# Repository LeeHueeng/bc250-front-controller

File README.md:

# BC250 Front Controller

**Turn your AMD BC-250 into a real PC** — smart power button, graceful shutdown, temperature-driven fan curve, OLED status display, and Home Assistant integration, all running standalone on a single ESP32-S3.

[🇰🇷 한국어 README](README.ko.md)

> ⚠️ **Status: work in progress.** Firmware boots and is verified on a bare board; full hardware validation (relay + sensors + fan on a live BC-250) is ongoing. Follow the repo for updates.

## Why?

The AMD BC-250 is a PS5-APU board that sells for roughly $100–150 these days — but it was born in a mining rack, so as a desktop it's missing everything:

- ❌ **No power button** and no ACPI — power on = PSU on
- ❌ **No graceful shutdown** — cutting power is the only "off"
- ❌ **No usable fan control** outside the original rack chassis
- ❌ **No status indication** whatsoever

This project fixes all of that with an ESP32-S3 sitting between your ATX PSU and the board — like the front panel the BC-250 never had.

## Features

- 🔌 **Real power button** — short press to power on / gracefully shut down, 5-second hold to force off
- 🛡️ **Fail-safe relay design** — the ATX `PS_ON` line is held through the relay's **NC contact**, so if the ESP32 crashes, reboots or updates, **your server stays up**
- 🧠 **Fully autonomous** — the graceful-shutdown sequence (HTTP request to the OS → wait → cut power), fan curve, OLED and button all run on the ESP32 itself. No Home Assistant, no cloud, no Wi-Fi required
- 🌡️ **Temperature-driven fan curve** — two DS18B20 probes (GPU heatsink + case), 25 kHz PWM, tach feedback with fan-failure detection
- 🖥️ **OLED status display** — power state, temperatures, fan RPM, network info on an SSD1306
- 🎛️ **On-device settings menu** — two extra buttons + the OLED give you a local menu: fan mode/preset, manual speed, display brightness, overheat threshold, shutdown timeout — all saved to flash, no phone or PC needed
- 🚨 **WS2812 status LED** — off / green (running) / yellow (shutting down) / red (fan failure, overheat)
- 🌐 **Built-in web dashboard** — control everything from a browser, straight from the ESP32
- 🏠 **Home Assistant auto-discovery** — appears natively via the ESPHome integration (optional MQTT)
- 📶 **Zero-config Wi-Fi provisioning** — first boot opens a `bc250-front-setup` AP with a captive portal; no credentials are baked into the firmware
- 🔄 **OTA updates** — flash over USB once, update over the air forever
- 📴 **Network-loss hardened** — never reboots on Wi-Fi/API loss; local control keeps working, the setup AP reopens automatically

## How it works

The BC-250 only uses the PCIe 8-pin — the ATX 24-pin connector is completely unused. So we steal three wires from it:

| ATX wire | Purpose |
|---|---|
| 🟣 Purple (pin 9, `5VSB`) | Always-on 5 V → powers the ESP32 + relay even when the PSU is "off" |
| 🟢 Green (pin 16, `PS_ON`) | Grounding this turns the PSU on — held via the relay **NC** contact |
| ⚪ Gray (pin 8, `PWR_OK`) | Tells the ESP32 whether the PSU is actually up (10k+10k divider) |

Graceful shutdown, with the **ESP32 as the source of truth** (no home-automation dependency):

```
button / web / HA  →  ESP32  →  HTTP shutdown request to the OS
                              →  wait 60 s for the OS to halt
                              →  release PS_ON (power off)
```

## Build tiers — everything is optional except the relay

Missing parts don't break anything: an absent OLED, sensor, fan or button simply disables that one feature. Start minimal, add parts whenever you feel like it.

| Tier | Hardware | You get | Firmware |
|---|---|---|---|
| **Minimal** | ESP32 + relay + 3 jumper wires | Web/HA power on-off, graceful shutdown, status LED (onboard) | [`bc250-front-minimal.yaml`](bc250-front-minimal.yaml) |
| **+ Button** | + push button | Physical front-panel power button | same |
| **Full** | + OLED, 2× DS18B20, PWM fan, 2 menu buttons, PWR_OK divider | Fan curve, temperatures, display, on-device settings menu, PSU state | [`bc250-front.yaml`](bc250-front.yaml) |
| **Full + color LCD** | Full, but OLED → **ST7789V 2.4" 240×320 SPI** | All of the above + large color UI, status icons, backlight dimming | [`bc250-front-st7789.yaml`](bc250-front-st7789.yaml) |

## Hardware

| Part | Qty | ~Cost |
|---|---|---|
| ESP32-S3 dev board (2×22 pins) | 1 | $5 |
| 5 V 1-channel relay module (optocoupler) | 1 | $1 |
| SSD1306 0.96" OLED (I2C) | 1 | $2 |
| DS18B20 temperature sensor | 2 | $2 |
| Momentary push button (power + 2 menu) | 3 | $1 |
| Resistors: 2× 10 kΩ, 1× 4.7 kΩ | — | $0.1 |
| Dupont jumper wires | — | $1 |

**No soldering required** — male jumper pins fit straight into the unused ATX 24-pin connector holes.

## PCB — three options (optional)

| | [**DIY carrier board**](hardware/bc250-front-carrier/README.md) | [**Semi-assembled PCBA**](hardware/bc250-front-pcba/README.md) | [**DevKit mini**](hardware/bc250-front-mini/README.md) |
|---|---|---|---|
| How | bare board, hand-solder the parts, plug in an ESP32-S3-DevKitC-1 | JLCPCB Economic assembly — you solder only the ESP32-S3 WROOM module, the display socket and (optionally) the LED | **66×50 mm**, smallest — DevKit on sockets, parts under it, LCD wired to a pin header |
| Power switch | relay | MOSFET (silent) | MOSFET (silent) |
| Sensors | DS18B20 | DS18B20 **or** 10 kΩ NTC | DS18B20 |
| Cost (5 boards) | ≈ $2 boards + ≈ $8 parts each | JLCPCB ≈ $45 + ≈ $4 module each → ≈ $13 each | ≈ $2 boards (≈ $12 with SMD assembly) + a DevKit |
| Firmware | `relay_inverted: "false"` | defaults + `log_uart: USB_SERIAL_JTAG` | defaults (`relay_inverted: "true"`) |

All three take the PSU's ATX 24-pin plug directly and use the pin map above.

## Wiring

| ESP32-S3 pin | Connects to |
|---|---|
| `5V` | ATX pin 9 — purple `5VSB` |
| `GND` | ATX black (common ground) |
| `3V3` | OLED VCC, DS18B20 VDD, pull-ups |
| `GPIO4` | Relay IN |
| `GPIO5` | ATX pin 8 — gray `PWR_OK` (**via 10k+10k divider**) |
| `GPIO6` | Power button (other leg → GND) |
| `GPIO7` | DS18B20 data ×2, 4.7 kΩ pull-up to 3.3 V |
| `GPIO8` / `GPIO9` | OLED SDA / SCL |
| `GPIO10` | Fan PWM (4-pin fan, pin 4) |
| `GPIO11` | Fan tach (4-pin fan, pin 3) |
| `GPIO12` / `GPIO13` | Menu buttons A (navigate) / B (select) — other leg → GND |
| `GPIO48` | WS2812 (onboard on most devkits) |

Relay contacts: **COM ↔ ATX pin 16 (green `PS_ON`)**, **NC ↔ GND**, NO unused.

Full interactive wiring guide (Korean): [`docs/wiring-guide.html`](docs/wiring-guide.html) (OLED) · [`docs/wiring-guide-st7789.html`](docs/wiring-guide-st7789.html) (ST7789V)

## Flashing

```bash
pip install esphome
esphome run bc250-front.yaml   # first time over USB, afterwards OTA
```

First boot: join the **`bc250-front-setup`** Wi-Fi AP from your phone → the captive portal opens → pick your network, enter the password. Done. Home Assistant will auto-discover the device within minutes.

> **Board note:** on CH343-based devkits the logger must use `hardware_uart: UART0` (already set in the YAML) — the default USB-JTAG console is not routed to the USB port on those boards.

## Roadmap

- [ ] OS-side shutdown agent (tiny systemd unit) + install script
- [ ] INA226 power monitoring (watts on the OLED!)
- [ ] Web-editable fan curve
- [ ] 3D-printable front-panel enclosure
- [ ] Buzzer alerts / event log

PRs and issues welcome — especially test reports from different BC-250 setups.

## Credits

- [mothenjoyer69/bc250-documentation](https://github.com/mothenjoyer69/bc250-documentation) — the definitive BC-250 hardware reference
- [elektricM/amd-bc250-docs](https://github.com/elektricM/amd-bc250-docs) — power & cooling documentation
- Built with [ESPHome](https://esphome.io)

## License

[MIT](LICENSE)

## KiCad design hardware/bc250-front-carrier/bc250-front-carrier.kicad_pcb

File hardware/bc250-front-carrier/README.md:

# BC250 Front Controller — carrier PCB v1.0

A carrier board for the ESP32-S3-DevKitC-1. **The PSU's ATX 24-pin plug goes straight onto the board**, so 5VSB / PS_ON / PWR_OK / 12V / GND are wired without jumper wires or hot glue. Every part is through-hole — a soldering iron is all you need.

[🇰🇷 한국어](README.ko.md)

| | |
|---|---|
| Size | 96 × 64 mm, 2 layers, 1.6 mm, 4× M3 holes (87 × 55 mm spacing) |
| MCU | ESP32-S3-DevKitC-1 (2×22 pins) in two female sockets |
| Power | ATX 24-pin header (Molex Mini-Fit Jr 5566-24A) on board |
| Relay | SRD-05VDC-SL-C + S8050 NPN driver on board — same **NC fail-safe** wiring as before |
| Display | ST7789 2.4″ SPI 8-pin socket **and** SSD1306 OLED 4-pin socket (fit either) |
| Other connectors | 4-pin PWM fan, 2× DS18B20, external WS2812, 6-pin front-panel buttons + 3 on-board tact switches |
| Checks | KiCad 10 ERC / DRC / schematic-PCB parity: **0 violations** (not yet verified on a physical board — see first power-up below) |

## Files

| File | Purpose |
|---|---|
| [`gerbers/bc250-front-carrier-v1.0-gerbers.zip`](gerbers/bc250-front-carrier-v1.0-gerbers.zip) | **upload this to JLCPCB** (Gerbers + Excellon drill + job file) |
| `bc250-front-carrier.kicad_pro` / `.kicad_sch` / `.kicad_pcb` | KiCad 10 project, footprint and symbol libraries included (opens anywhere) |
| [`bc250-front-carrier-schematic.pdf`](bc250-front-carrier-schematic.pdf) | schematic |
| [`bom.csv`](bom.csv) | bill of materials |
| `bc250-front-carrier-pos.csv` | component positions (assembly reference) |
| `images/` | top / bottom / iso renders, layout SVG, schematic SVG |
| [`../tools/`](../tools/) | regenerates the whole board from scripts (`build.sh`) |

## Ordering at JLCPCB

1. [jlcpcb.com](https://jlcpcb.com) → **Order now** → *Add gerber file* → upload `gerbers/bc250-front-carrier-v1.0-gerbers.zip`
2. It is detected as 96 × 64 mm, 2 layers. Keep the **defaults**: FR-4, 1.6 mm, 1 oz, HASL, quantity 5 (colour is up to you, Remove Order Number: No).
3. No SMT assembly needed — everything is hand-soldered.
4. Expect roughly $2 for 5 boards plus shipping.

## BOM

| Ref | Qty | Part | Notes |
|---|---|---|---|
| U1 | 1 | ESP32-S3-DevKitC-1 (N8R2 / N16R8, either) | with male pin headers soldered |
| U1 sockets | 2 | 1×22 female pin socket 2.54 mm | solder with the DevKit plugged in for alignment |
| J1 | 1 | ATX 24-pin motherboard header (Molex 5566-24A / 39-28-1243 or compatible, 4.2 mm 2×12 vertical) | |
| K1 | 1 | SRD-05VDC-SL-C relay (Songle / Sanyou SRD) | |
| Q1 | 1 | S8050 NPN (2N2222A / BC337 also fine) | TO-92, E-B-C |
| D1 | 1 | 1N4148 | cathode band toward the **K** mark |
| R1 | 1 | 1 kΩ | |
| R2, R3, R4 | 3 | 10 kΩ | |
| R5 | 1 | 4.7 kΩ | |
| C1 | 1 | 100 µF 16 V electrolytic (5 mm) | long leg (+) to the **+** mark |
| C2 | 1 | 100 nF ceramic | |
| J2 | 1 | 1×8 female pin socket | ST7789 LCD module plugs in directly |
| J3 | 1 | 1×4 female pin socket | SSD1306 OLED module plugs in directly |
| J4 | 1 | 1×4 male pin header | 4-pin fan (a real fan header fits too) |
| J5, J6, J7 | 3 | 1×3 male pin header | 2× DS18B20, WS2812 |
| J8 | 1 | 1×6 male pin header | front-panel buttons (optional) |
| SW1–SW3 | 3 | 6×6 mm tactile switch | on-board PWR / A / B |
| H1–H4 | 4 | M3 standoffs | optional |

## Assembly order

1. **Low parts first**: R1–R5 → D1 (band to `K`) → Q1 (flat side as drawn on the silkscreen) → C2 → C1 (mind the `+`)
2. **Sockets and headers**: J2/J3 female sockets, J4–J8 pin headers, SW1–SW3, the two 1×22 sockets for U1
3. **Big parts**: K1 relay, J1 ATX header — the latch ramp faces the top board edge (the `ATX 24-pin ← PSU plug` text)

## ⚠️ First power-up — **before** fitting the ESP32

The ATX header pin numbering follows KiCad's standard Molex 5566-24A footprint, but no physical board has been verified yet. This takes a minute:

1. Plug in the PSU's 24-pin **without** the DevKit and switch the PSU on. The relay is idle (NC), so **the PSU turning on immediately is correct** — that is the fail-safe.
2. With a multimeter (also printed on the back silkscreen):
   - U1 socket, top row `5V` pin ↔ `GND` = **about 5 V**
   - `FAN` header `12V` pin ↔ `GND` = **12 V**
   - If the `5V` pin reads 0 V or 12 V, **stop** and check J1 orientation/solder joints.
3. Power the PSU off and fit the DevKit: USB connectors toward the **left board edge** (`USB` silkscreen), antenna toward the relay.

## Firmware

- Set **`relay_inverted: "false"`** under `substitutions:` in the yaml (this board drives the relay with an NPN, active-high; off-the-shelf relay modules are `"true"`).
- If you attach an external WS2812 to J7, adjust `num_leds` in `light:` (the DevKit's on-board LED is pixel 0).
- Everything else matches the [wiring guide](../../docs/wiring-guide.html) — the board simply implements that wiring.

## Design notes

- **Relay**: COM=PS_ON, NC=GND. PS_ON is grounded at rest, so the PSU is on. GPIO4 HIGH → Q1 → coil energised → NC opens → PSU off. R2 (10 k) keeps the coil off while the ESP32 boots; D1 clamps the flyback. NO is left open.
- **PWR_OK**: 5 V → R3/R4 10 k/10 k → 2.5 V → GPIO5.
- **1-Wire**: GPIO7 with R5 4.7 k to 3V3; both DS18B20s in parallel on J5/J6.
- **Power**: 5VSB → DevKit `5V` pin (on-board LDO) + relay coil (C1 100 µF). 3V3 from the DevKit LDO feeds J2/J3/J5/J6/R5. 12 V is fan-only (present only while the PSU is on).
- **Layout**: 0.3 mm signals, 0.7 mm power, GND pours on both sides, copper keep-out under the WROOM antenna. Autorouted with Freerouting, DRC clean.

## Regenerating

Rather than editing the `.kicad_pcb` by hand, change `../tools/gen_pcb.py` (placement, nets) or `gen_sch.py` (schematic) and run `../tools/build.sh`. It needs KiCad 10 and Java 21+; Freerouting is downloaded automatically. The outputs are installed back into this folder.

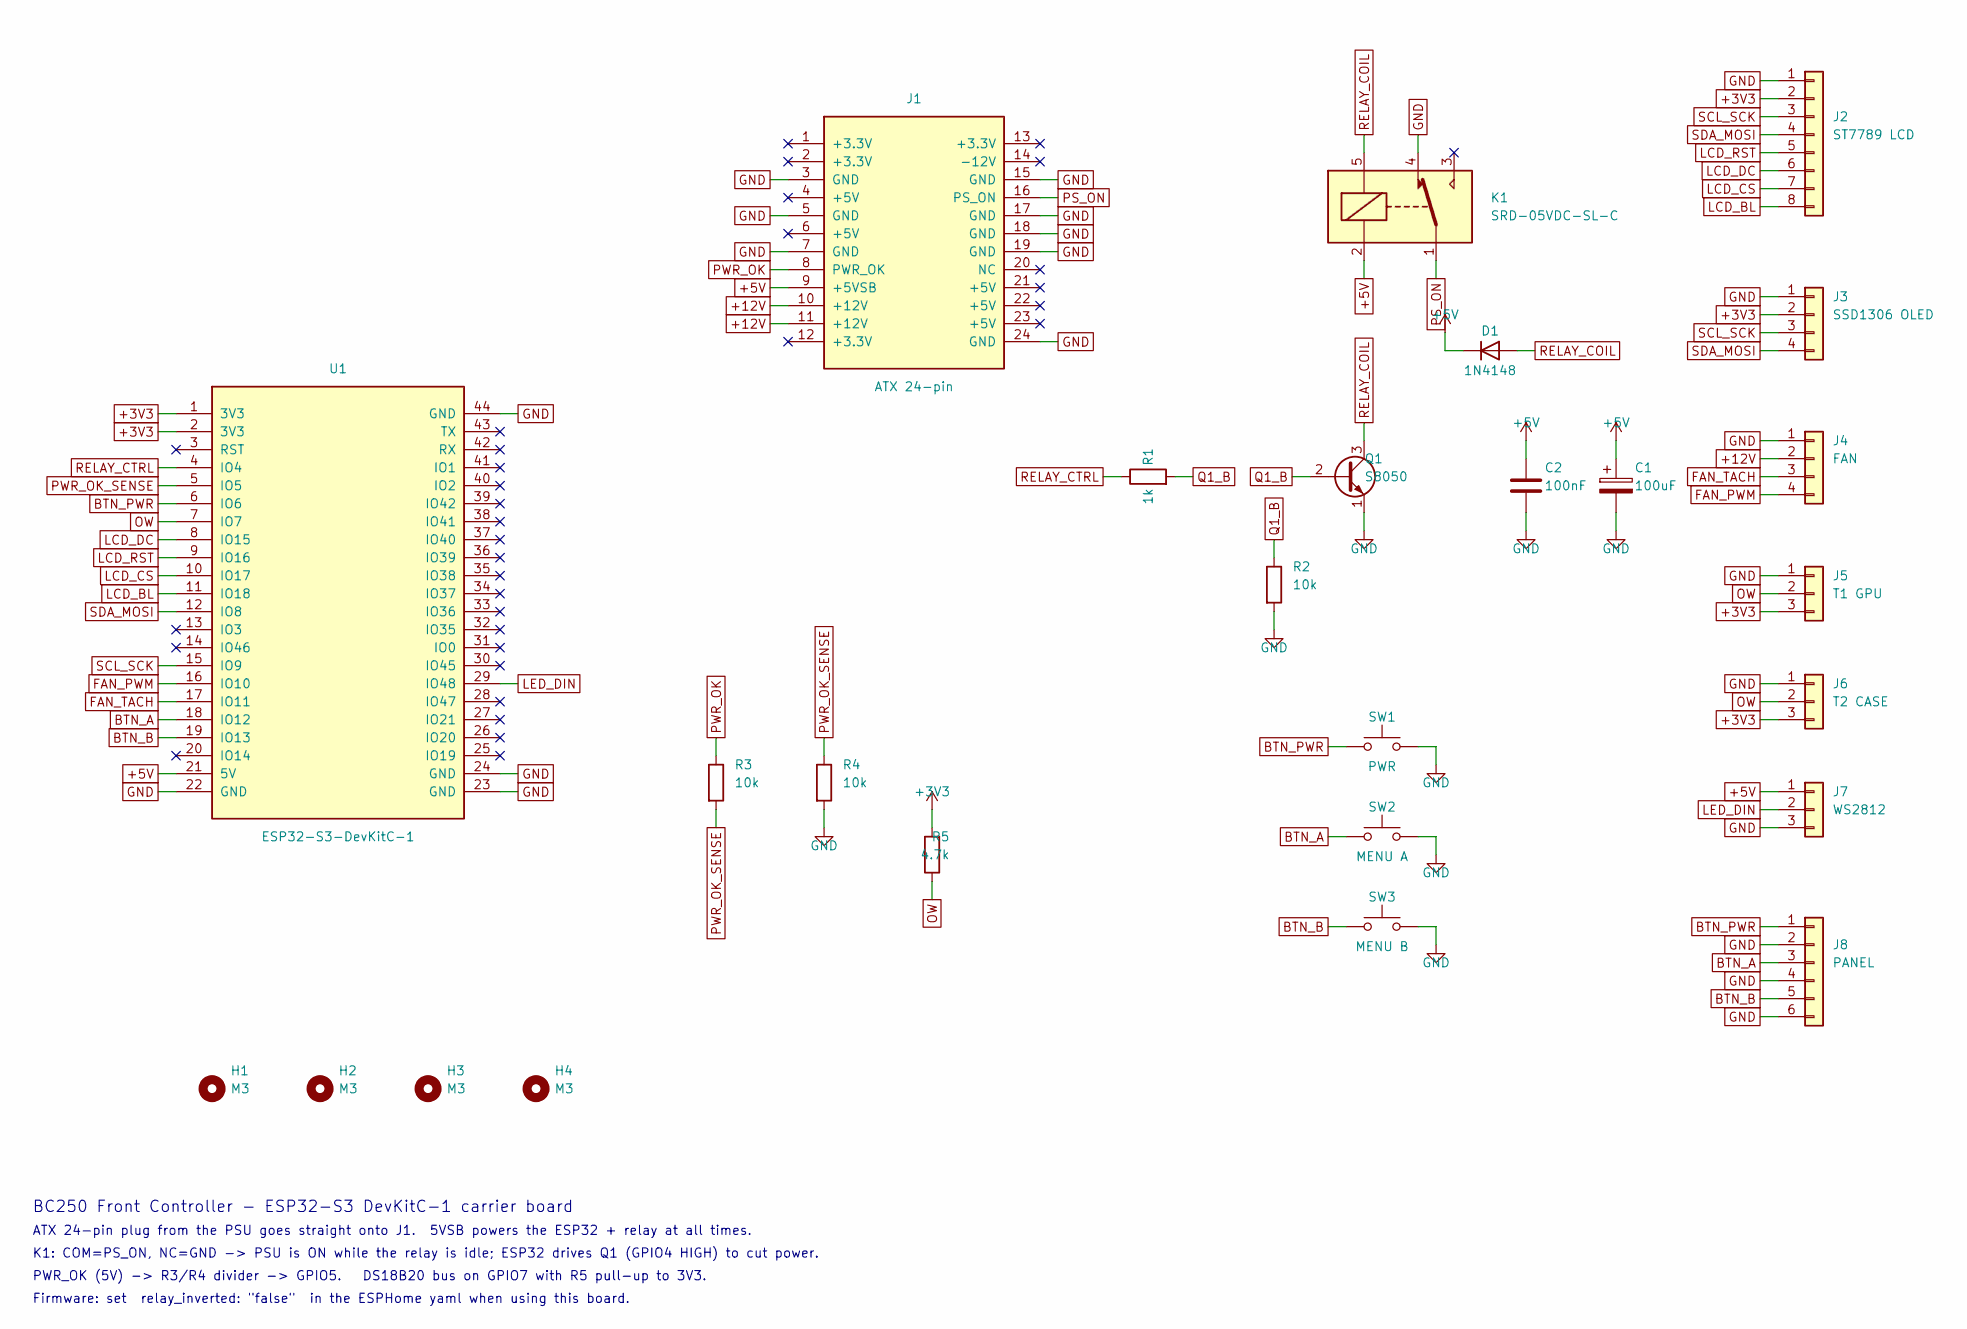
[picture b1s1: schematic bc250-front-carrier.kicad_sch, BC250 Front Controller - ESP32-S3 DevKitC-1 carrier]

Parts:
C1: 100uF; CP_Radial_D5.0mm_P2.00mm
C2: 100nF; C_Disc_D5.0mm_W2.5mm_P2.50mm
D1: 1N4148; D_DO-35_SOD27_P7.62mm_Horizontal
H1, H2, H3, H4: M3; MountingHole_3.2mm_M3
J1: ATX 24-pin; Molex_Mini-Fit_Jr_5566-24A_2x12_P4.20mm_Vertical
J2: ST7789 LCD; PinSocket_1x08_P2.54mm_Vertical
J3: SSD1306 OLED; PinSocket_1x04_P2.54mm_Vertical
J4: FAN; PinHeader_1x04_P2.54mm_Vertical
J5: T1 GPU; PinHeader_1x03_P2.54mm_Vertical
J6: T2 CASE; PinHeader_1x03_P2.54mm_Vertical
J7: WS2812; PinHeader_1x03_P2.54mm_Vertical
J8: PANEL; PinHeader_1x06_P2.54mm_Vertical
K1: SRD-05VDC-SL-C; Relay_SPDT_SANYOU_SRD_Series_Form_C
Q1: S8050; TO-92_Inline
R1: 1k; R_Axial_DIN0207_L6.3mm_D2.5mm_P7.62mm_Horizontal
R2, R3, R4: 10k; R_Axial_DIN0207_L6.3mm_D2.5mm_P7.62mm_Horizontal
R5: 4.7k; R_Axial_DIN0207_L6.3mm_D2.5mm_P7.62mm_Horizontal
SW1: PWR; SW_PUSH_6mm
SW2: MENU A; SW_PUSH_6mm
SW3: MENU B; SW_PUSH_6mm
U1: ESP32-S3-DevKitC-1; ESP32-S3-DevKitC-1_Socket

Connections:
+3V3: J2.2, J3.2, J5.3, J6.3, R5.2, U1.1 (3V3), U1.2 (3V3)
+5V: C1.1, C2.1, D1.1 (K), J1.9 (+5VSB), J7.1, K1.2, U1.21 (5V)
+12V: J1.10 (+12V), J1.11 (+12V), J4.2
BTN_A: J8.3, SW2.1, U1.18 (IO12)
BTN_B: J8.5, SW3.1, U1.19 (IO13)
BTN_PWR: J8.1, SW1.1, U1.6 (IO6)
FAN_PWM: J4.4, U1.16 (IO10)
FAN_TACH: J4.3, U1.17 (IO11)
GND: C1.2, C2.2, J1.3 (GND), J1.5 (GND), J1.7 (GND), J1.15 (GND), J1.17 (GND), J1.18 (GND), J1.19 (GND), J1.24 (GND), J2.1, J3.1, J4.1, J5.1, J6.1, J7.3, J8.2, J8.4, J8.6, K1.4, Q1.1 (E), R2.2, R4.2, SW1.2, SW2.2, SW3.2, U1.22 (GND), U1.23 (GND), U1.24 (GND), U1.44 (GND)
LCD_BL: J2.8, U1.11 (IO18)
LCD_CS: J2.7, U1.10 (IO17)
LCD_DC: J2.6, U1.8 (IO15)
LCD_RST: J2.5, U1.9 (IO16)
LED_DIN: J7.2, U1.29 (IO48)
OW: J5.2, J6.2, R5.1, U1.7 (IO7)
PS_ON: J1.16 (PS_ON), K1.1
PWR_OK: J1.8 (PWR_OK), R3.1
PWR_OK_SENSE: R3.2, R4.1, U1.5 (IO5)
Q1_B: Q1.2 (B), R1.2, R2.1
RELAY_COIL: D1.2 (A), K1.5, Q1.3 (C)
RELAY_CTRL: R1.1, U1.4 (IO4)
SCL_SCK: J2.3, J3.3, U1.15 (IO9)
SDA_MOSI: J2.4, J3.4, U1.12 (IO8)

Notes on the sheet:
BC250 Front Controller - ESP32-S3 DevKitC-1 carrier board
ATX 24-pin plug from the PSU goes straight onto J1. 5VSB powers the ESP32 + relay at all times.
K1: COM=PS_ON, NC=GND -> PSU is ON while the relay is idle; ESP32 drives Q1 (GPIO4 HIGH) to cut power.
PWR_OK (5V) -> R3/R4 divider -> GPIO5. DS18B20 bus on GPIO7 with R5 pull-up to 3V3.
Firmware: set relay_inverted: "false" in the ESPHome yaml when using this board.

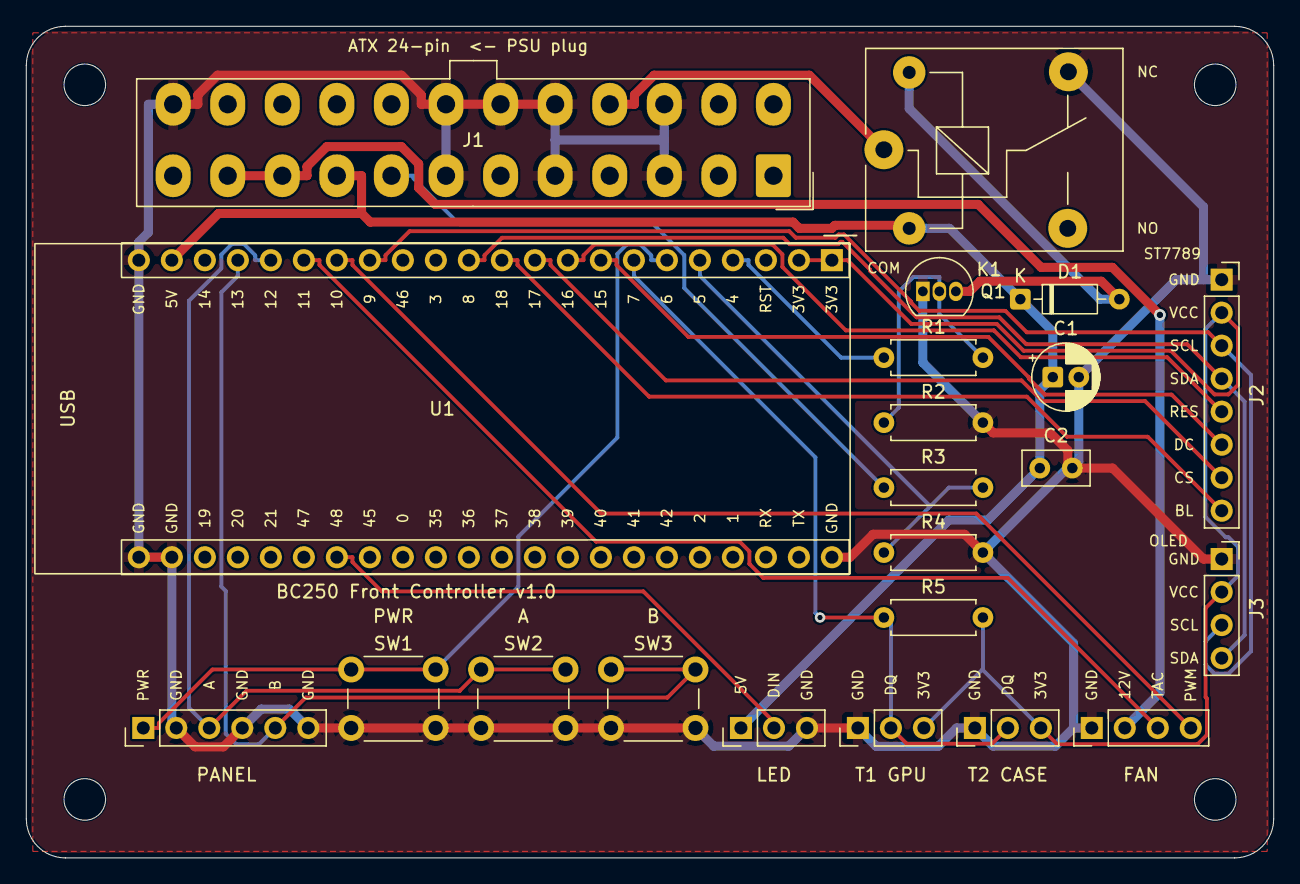
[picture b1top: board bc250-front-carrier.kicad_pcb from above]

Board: 2 copper layers, 96.0 x 64.0 mm, 26 parts (0 on the bottom side), 23 nets.

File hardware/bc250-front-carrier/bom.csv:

Ref,Qty,Value,Description,Package / footprint,Notes
U1,1,ESP32-S3-DevKitC-1,ESP32-S3 dev board (N8R2 / N16R8 all fine),2x22 pins 2.54 mm,"buy with male pin headers soldered; plugs into the two 1x22 sockets"
U1 socket,2,1x22 female pin socket 2.54 mm,for the DevKit,THT,"solder with the DevKit plugged in for alignment"
J1,1,ATX 24-pin motherboard header,Molex Mini-Fit Jr 5566-24A / 39-28-1243 (4.2 mm 2x12 vertical) or compatible,THT,"KR: 디바이스마트/엘레파츠 'ATX 24핀 보드용 커넥터'; latch ramp toward the board edge"
K1,1,SRD-05VDC-SL-C,5 V SPDT relay (Songle / Sanyou SRD),THT 19x15.5 mm,
Q1,1,S8050,NPN transistor (2N2222A / BC337 also OK),TO-92 (E-B-C),"flat side per silkscreen"
D1,1,1N4148,flyback diode,DO-35,"cathode band toward the 'K' mark (pin 1, +5V side)"
R1,1,1 kΩ 1/4 W,base resistor,axial 7.62 mm,
"R2,R3,R4",3,10 kΩ 1/4 W,base pull-down / PWR_OK divider,axial 7.62 mm,
R5,1,4.7 kΩ 1/4 W,DS18B20 1-wire pull-up,axial 7.62 mm,
C1,1,100 µF 16 V electrolytic,5VSB bulk,radial D5 mm P2.0 mm,"long leg (+) to the '+' mark"
C2,1,100 nF ceramic,decoupling,disc P2.5 mm,
J2,1,1x8 female pin socket 2.54 mm,ST7789V 2.4" SPI LCD module (GND VCC SCL SDA RES DC CS BL),THT,
J3,1,1x4 female pin socket 2.54 mm,SSD1306 0.96" I2C OLED (GND VCC SCL SDA),THT,
J4,1,1x4 male pin header 2.54 mm,4-pin PWM fan (GND 12V TACH PWM),THT,"a real 4-pin fan header (KK-254 style) also fits"
"J5,J6",2,1x3 male pin header 2.54 mm,DS18B20 probes (GND DQ 3V3),THT,
J7,1,1x3 male pin header 2.54 mm,external WS2812 (5V DIN GND),THT,optional
J8,1,1x6 male pin header 2.54 mm,front-panel buttons (PWR GND A GND B GND),THT,optional
"SW1,SW2,SW3",3,6x6 mm tactile switch,on-board PWR / MENU A / MENU B,THT 4-leg,
"H1-H4",4,M3 standoff + screw,mounting (87 x 55 mm hole spacing),3.2 mm holes,optional

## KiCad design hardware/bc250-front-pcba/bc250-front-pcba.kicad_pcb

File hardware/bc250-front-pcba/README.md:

# BC250 Front Controller — semi-assembled PCBA v1.0 (JLCPCB Economic assembly)

JLCPCB places every resistor, capacitor, the MOSFET, LDO, USB-C, ATX header, pin headers and buttons; **you hand-solder three parts: the ESP32-S3 module, the display socket and (optionally) the status LED.** Leaving those out lets JLCPCB use the cheap **Economic** assembly (the ESP32 module and 5050 LEDs are "Standard only" parts), which cuts the fixed fees by about $22.

[🇰🇷 한국어](README.ko.md) · fully hand-soldered DevKit version: [`../bc250-front-carrier/`](../bc250-front-carrier/README.md)

| | |
|---|---|
| Size | 90 × 56 mm, 2 layers, 1.6 mm, 4× M3 |
| MCU | **ESP32-S3-WROOM-1** module (hand-soldered; any of N4/N8/N8R2/N16R8) + USB-C native USB (no USB-serial chip) |
| Power switch | **MOSFET (AO3400A)** grounds PS_ON — no relay, silent, same fail-safe (PSU stays on when the ESP32 is dead) |
| Power | 5VSB from the ATX header → AMS1117-3.3. 12 V is fan-only |
| Display | 1×8 socket position (hand-soldered) for the **ST7789 (8 pins) or SSD1306 OLED (first 4 pins)** |
| Sensors | T1/T2 3-pin headers — DS18B20 **or 10 kΩ NTC** (4.7 k pull-ups on board) |
| Other | 4-pin PWM fan, WS2812B status LED position (optional) + external LED header, 4-pin front-panel header, PWR/A/B/BOOT/RESET buttons |
| Checks | KiCad 10 ERC / DRC / schematic-PCB parity: 0 violations. **Not verified on hardware yet** — follow the first power-up steps |

## Files

| File | Purpose |
|---|---|
| [`gerbers/bc250-front-pcba-v1.0-gerbers.zip`](gerbers/bc250-front-pcba-v1.0-gerbers.zip) | JLCPCB step 1: Gerbers |
| [`jlcpcb-bom.csv`](jlcpcb-bom.csv) · [`jlcpcb-cpl.csv`](jlcpcb-cpl.csv) | JLCPCB step 2: **default (semi-assembled)** BOM/CPL — U1, J2, LED1 excluded |
| `jlcpcb-bom-full.csv` · `jlcpcb-cpl-full.csv` | if you want everything placed (needs Standard assembly, ≈ +$30) |
| `bc250-front-pcba.kicad_pro` / `.kicad_sch` / `.kicad_pcb` | KiCad 10 project (libraries included) |
| [`bc250-front-pcba-schematic.pdf`](bc250-front-pcba-schematic.pdf) | schematic |
| `images/` | renders, layout and schematic SVG |
| [`../tools/`](../tools/) | `build.sh pcba` regenerates everything |

## Ordering at JLCPCB

1. [jlcpcb.com](https://jlcpcb.com) → **Order now** → upload `gerbers/bc250-front-pcba-v1.0-gerbers.zip`. PCB options: defaults (FR-4, 1.6 mm, HASL). Quantity **at least 2**, 5 recommended.
2. **PCB Assembly** on → **Economic** · Top side · assembly quantity = board quantity.
3. **Add BOM / CPL**: upload `jlcpcb-bom.csv` + `jlcpcb-cpl.csv` → all 22 lines should auto-match LCSC parts. (Extended parts: ATX header, USB-C, two pin-header types = 4; everything else is Basic.)
4. **Placement preview**: `J3` USB-C opening toward the **bottom edge**; `Q1` (SOT-23), `U2` (SOT-223), `D1`/`D2` matching the silkscreen. Rotate in the preview if not.
5. Pay → 1–2 weeks.

### Cost (estimate for 5 boards, Aug 2026 — the JLCPCB quote is authoritative)

| Item | Amount |
|---|---|
| PCB ×5 | ~$2 |
| Economic assembly setup + stencil | ~$8 + ~$1.5 |
| Extended-part loading fee ×4 | ~$12 |
| placed parts (≈ $2.6 / board) | ~$13 |
| assembly SMT + THT (≈ $1.7 / board) | ~$8.5 |
| **JLCPCB total (5)** | **≈ $45 + shipping → ≈ $9 each** |
| **JLCPCB total (2)** | **≈ $32 + shipping** |
| + bought separately: ESP32-S3-WROOM-1 (~$3.5), 1×8 female socket, WS2812B 5050 (optional) | ≈ $4 each |

→ **≈ $13 per board + display, sensors, fan.** Fully assembled (Standard, `*-full.csv`) is ≈ $100 for 5.

### Cost reductions in this version

| Item | Before | After |
|---|---|---|
| Assembly tier | Standard ($25 + $7) | **Economic ($8 + $1.5)** — only the module and LED are hand-soldered |
| Relay + driver (SRD-05V, S8050, 1N4148, 100 µF) | ~$0.7 + 4 THT parts | **one AO3400A MOSFET** ($0.09), silent |
| DevKit ($4.5–5) | 2 sockets + separate purchase | **WROOM module** ($3.5) + USB-C ($0.31) + LDO ($0.12) |
| THT R/C | 7 THT parts | **0603/0805 Basic parts** (no loading fee) |
| OLED socket + LCD socket | 2 parts | **one 1×8 socket** (OLED on the first 4 pins) |
| Front-panel header 1×6 | 1 extended part | **1×4** → same part as the fan header |
| Tact switches | 6×6 THT | **TS-1187A SMD (Basic, $0.02)** ×5 |
| Temperature sensors | 2× DS18B20 (~$2 each) | **10 kΩ NTC also supported** (~$0.2 each) |
| ESP32-S3 | N16R8 | **N4/N8 fine too** (no PSRAM needed) — you buy it, pick the cheapest |

ESP32-C3 was not adopted: the full build needs 15 GPIOs, the C3 exposes 13, and the saving is under $1. Possible for OLED/minimal-only builds.

## The three parts you solder

| Part | How |
|---|---|
| **U1 ESP32-S3-WROOM-1** | Iron-solder the edge castellations (1.27 mm pitch): flux → tack two corners to align → the rest. The large centre GND pad is **optional** (GND is also on edge pins 1/40; use hot air if you have it). Antenna toward the left board edge (see the silkscreen antenna outline). |
| **J2 display** | Solder a 1×8 2.54 mm female socket and plug the module in (recommended), or solder the module's pin header straight to the board. The OLED goes on the GND·VCC·SCL·SDA positions. |
| **LED1 WS2812B** (optional) | 5050, 4 pads, pin-1 mark (silk `1`) top-left. If you skip it, the external `LED` header (J7) carries the same data line, so nothing is lost. |

## Using it

### Firmware (same yaml, two substitutions)
```yaml
substitutions:
  relay_inverted: "true"        # same polarity as the relay module (GPIO4 LOW = power cut)
  log_uart: USB_SERIAL_JTAG     # logs over native USB
```
GPIO numbers are identical to the DevKit wiring — `bc250-front.yaml`, `bc250-front-st7789.yaml`, `bc250-front-minimal.yaml` flash unchanged. First flash over USB-C (`esphome run`), OTA afterwards. If auto-download does not trigger, hold **BOOT** and tap **RESET**. With only an external LED keep `num_leds: 1` (it shows the same pixel 0 as LED1).

### Temperature sensors — DS18B20 or NTC
- **Two DS18B20 (default)**: T1 and T2 on the GPIO7 1-Wire bus. Yaml unchanged.
- **Two NTCs (cheapest)**: move solder jumper **JP1** on the back from `1-2` (default, silk "7") to `2-3` (silk "2") so T2 gets its own channel on GPIO2. Wire each NTC between SIG and GND and replace `one_wire`/`dallas_temp` with:
  ```yaml
  sensor:
    - platform: adc
      pin: GPIO7            # T1 (T2: GPIO2)
      id: t1_adc
      attenuation: 12db
      update_interval: 5s
    - platform: resistance
      sensor: t1_adc
      configuration: DOWNSTREAM   # NTC to GND, 4.7k pull-up to 3V3
      resistor: 4.7kOhm
      reference_voltage: 3.3V
      id: t1_res
    - platform: ntc
      sensor: t1_res
      id: gpu_temp
      name: "GPU temperature"
      calibration:
        b_constant: 3950
        reference_temperature: 25°C
        reference_resistance: 10kOhm
  ```

### Connectors
| Label | Pins | Note |
|---|---|---|
| `LCD / OLED` (J2) | GND VCC SCL SDA RES DC CS BL | all 8 for ST7789 / first 4 for the OLED |
| `FAN` (J4) | GND 12V TACH PWM | 4-pin PWM fan |
| `T1` `T2` (J5 J6) | GND SIG 3V3 | DS18B20 (GND DQ VDD) or NTC (GND–SIG) |
| `LED` (J7) | 5V DIN GND | external WS2812, in parallel with LED1 (pixel 0) |
| `PANEL` (J8) | PWR A B GND | front buttons, in parallel with the on-board ones |
| `UART` (J9, not populated) | TX RX GND | debug |

### ⚠️ First power-up
1. **Before** soldering the module: plug in the PSU 24-pin only and switch the PSU on → **the PSU turning on immediately is correct** (fail-safe).
2. Check `T1` `3V3`–`GND` = 3.3 V, `FAN` `12V` = 12 V, `LED` `5V` = 5 V (also printed on the back). If fine, power off and solder the module.
3. Connect USB-C → `esphome run` → switch "server power" off in the web dashboard → the PSU should turn off.

## Design notes
- **PS_ON**: Q1 drain → PS_ON, source → GND, gate ← GPIO4 with R1 10 k pull-up to 3V3. While the ESP32 is in reset/download/dead the pull-up holds the gate high → PSU on. Firmware drives GPIO4 low → PSU off. Same logic as the active-low relay module, hence `relay_inverted: "true"`.
- **USB**: VBUS → D1 (B5819W) → 5 V rail: runs from USB alone, and the PSU's 5VSB never back-feeds the USB host. D+/D− pad pairs of the receptacle are bridged with locked tracks.
- **LED**: WS2812B VDD dropped to ~4.3 V through D2 (1N4148W) so 3.3 V data is a valid high. J7 shares the same data line (parallel).
- **BOOT/RESET**: R7/R6 10 k pull-ups, C5 1 µF EN delay.
- **Antenna**: module antenna toward the left board edge, copper removed on both layers underneath.
- **CPL rotations**: corrected by comparing pin-1 positions of the KiCad footprints against the JLCPCB (EasyEDA) footprints of the exact LCSC parts (SOT-23 / SOT-223 +180°, everything else 0°).

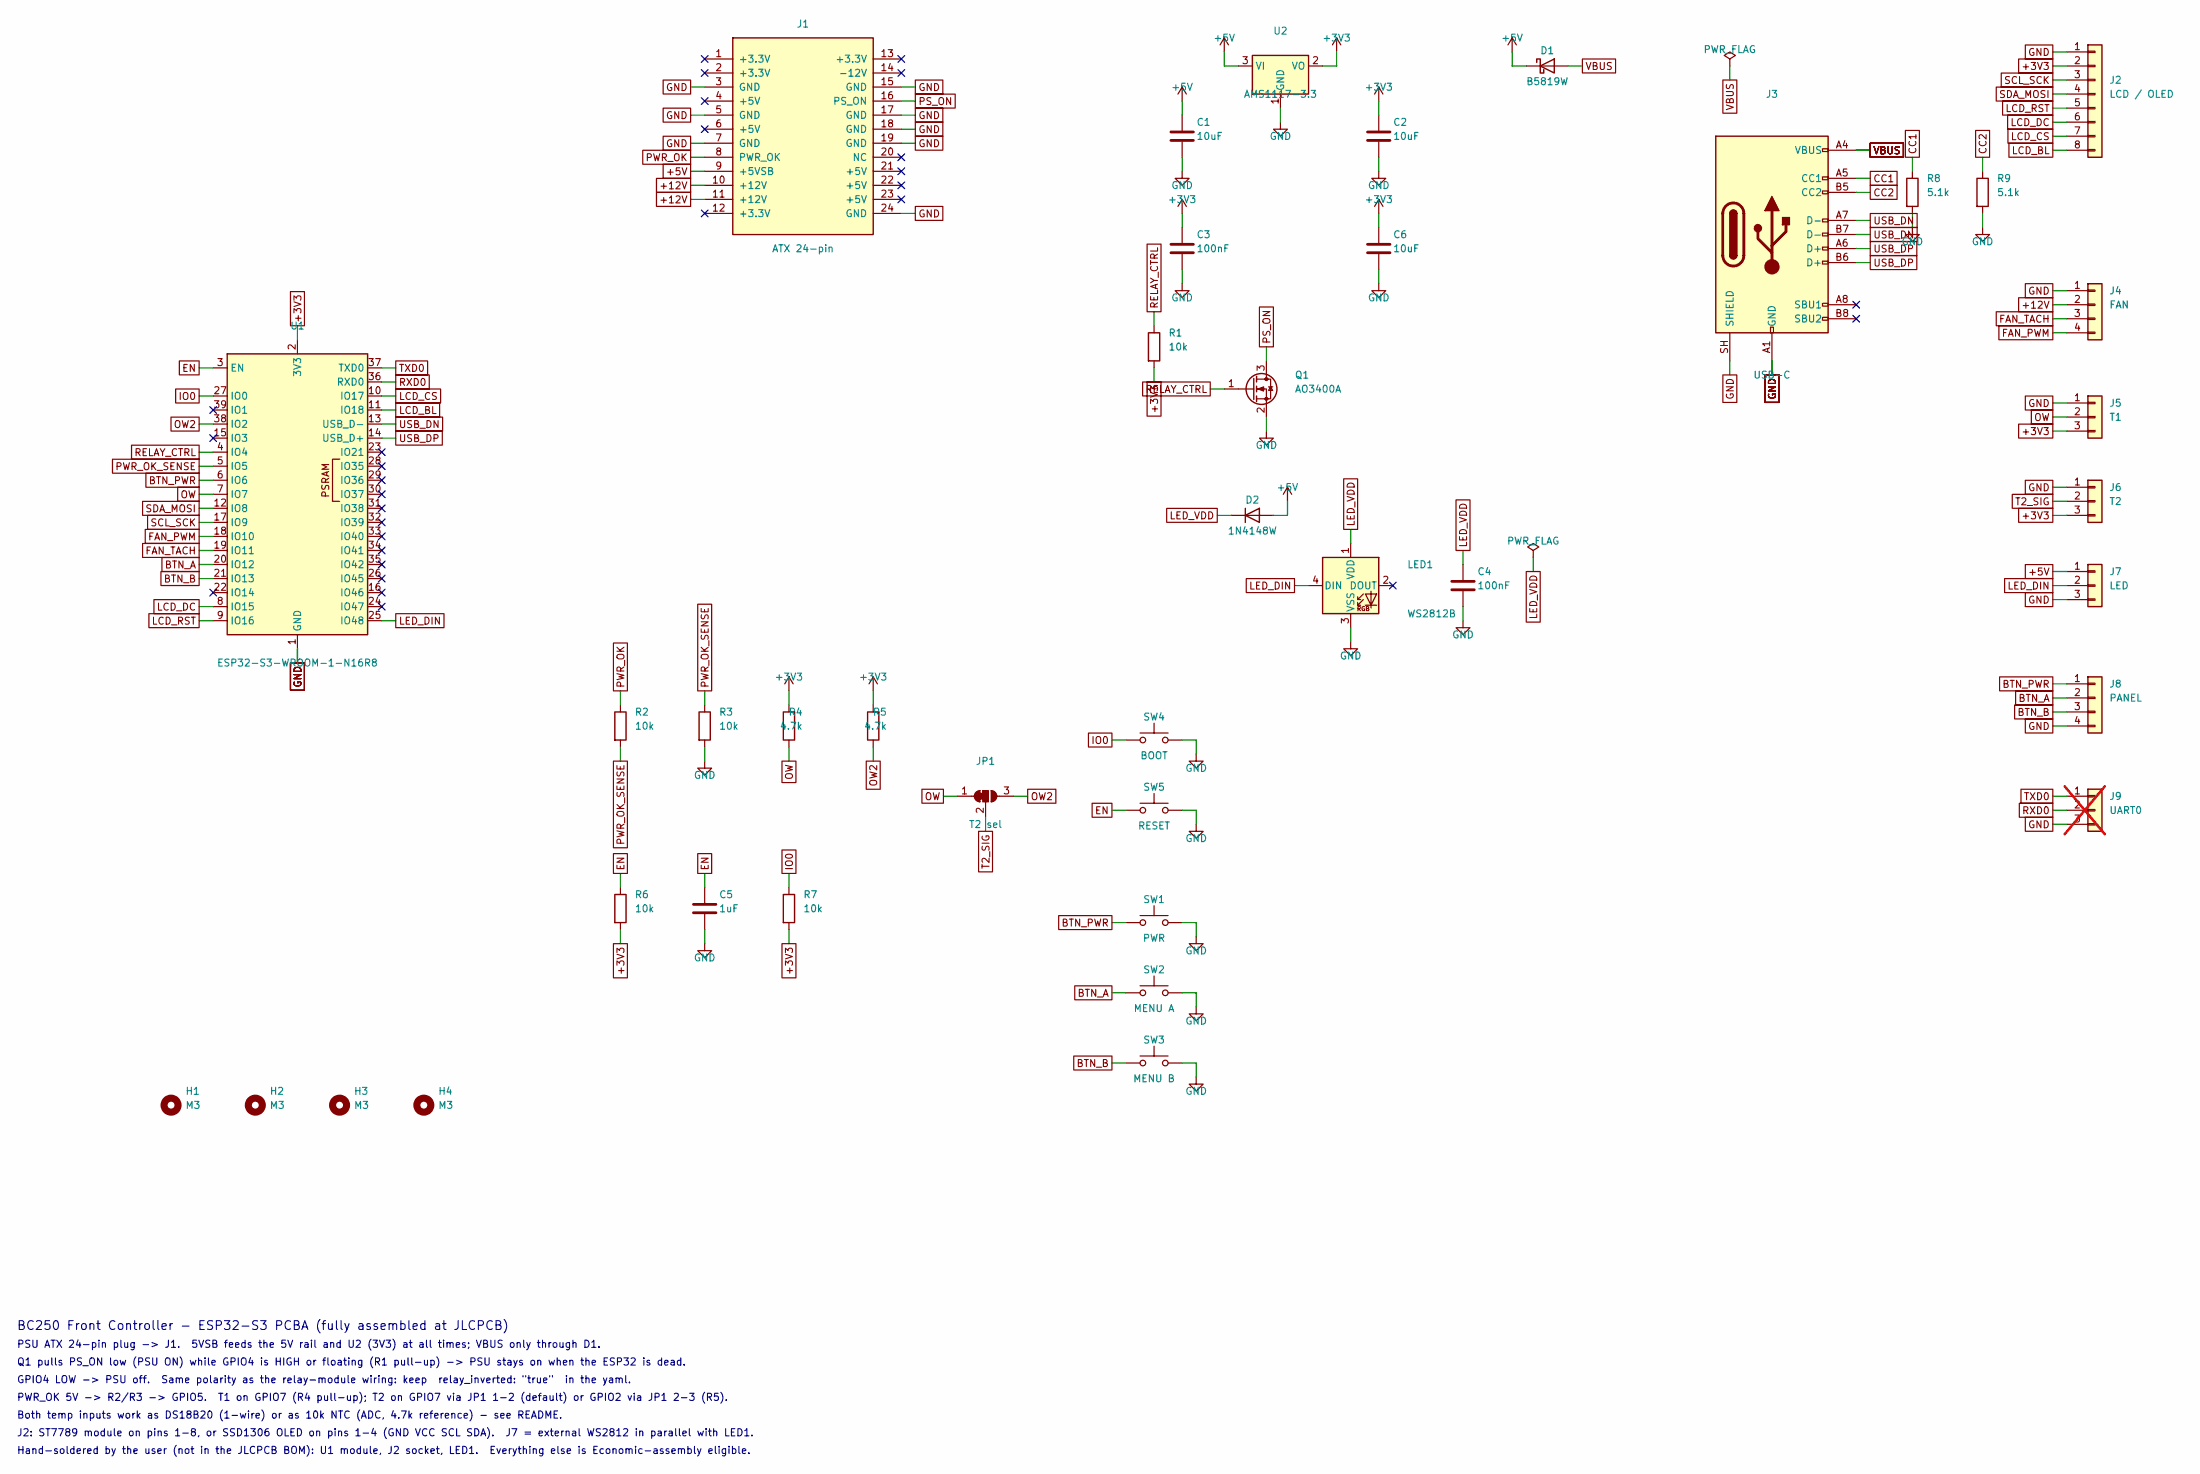
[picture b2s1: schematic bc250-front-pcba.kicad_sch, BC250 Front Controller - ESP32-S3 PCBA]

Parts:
C1, C2, C6: 10uF; C_0805_2012Metric
C3, C4: 100nF; C_0603_1608Metric
C5: 1uF; C_0603_1608Metric
D1: B5819W; D_SOD-123
D2: 1N4148W; D_SOD-123
H1, H2, H3, H4: M3; MountingHole_3.2mm_M3
J1: ATX 24-pin; Molex_Mini-Fit_Jr_5566-24A_2x12_P4.20mm_Vertical
J2: LCD / OLED; PinSocket_1x08_P2.54mm_Vertical
J3: USB-C; USB_C_Receptacle_HRO_TYPE-C-31-M-12
J4: FAN; PinHeader_1x04_P2.54mm_Vertical
J5: T1; PinHeader_1x03_P2.54mm_Vertical
J6: T2; PinHeader_1x03_P2.54mm_Vertical
J7: LED; PinHeader_1x03_P2.54mm_Vertical
J8: PANEL; PinHeader_1x04_P2.54mm_Vertical
J9: UART0; PinHeader_1x03_P2.54mm_Vertical; not fitted
JP1: T2 sel; SolderJumper-3_P1.3mm_Bridged12_Pad1.0x1.5mm
LED1: WS2812B; LED_WS2812B_PLCC4_5.0x5.0mm_P3.2mm
Q1: AO3400A; SOT-23
R1, R2, R3, R6, R7: 10k; R_0603_1608Metric
R4, R5: 4.7k; R_0603_1608Metric
R8, R9: 5.1k; R_0603_1608Metric
SW1: PWR; SW_TS-1187A
SW2: MENU A; SW_TS-1187A
SW3: MENU B; SW_TS-1187A
SW4: BOOT; SW_TS-1187A
SW5: RESET; SW_TS-1187A
U1: ESP32-S3-WROOM-1-N16R8; ESP32-S3-WROOM-1_edge
U2: AMS1117-3.3; SOT-223-3_TabPin2

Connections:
+3V3: C2.1, C3.1, C6.1, J2.2, J5.3, J6.3, R1.2, R4.2, R5.2, R6.2, R7.2, U1.2 (3V3), U2.2 (VO)
+5V: C1.1, D1.1 (K), D2.2 (A), J1.9 (+5VSB), J7.1, U2.3 (VI)
+12V: J1.10 (+12V), J1.11 (+12V), J4.2
BTN_A: J8.2, SW2.1, U1.20 (IO12)
BTN_B: J8.3, SW3.1, U1.21 (IO13)
BTN_PWR: J8.1, SW1.1, U1.6 (IO6)
CC1: J3.A5 (CC1), R8.1
CC2: J3.B5 (CC2), R9.1
EN: C5.1, R6.1, SW5.1, U1.3 (EN)
FAN_PWM: J4.4, U1.18 (IO10)
FAN_TACH: J4.3, U1.19 (IO11)
GND: C1.2, C2.2, C3.2, C4.2, C5.2, C6.2, J1.3 (GND), J1.5 (GND), J1.7 (GND), J1.15 (GND), J1.17 (GND), J1.18 (GND), J1.19 (GND), J1.24 (GND), J2.1, J3.A1 (GND), J3.A12 (GND), J3.B1 (GND), J3.B12 (GND), J3.SH (SHIELD), J4.1, J5.1, J6.1, J7.3, J8.4, J9.3, LED1.3 (VSS), Q1.2 (S), R3.2, R8.2, R9.2, SW1.2, SW2.2, SW3.2, SW4.2, SW5.2, U1.1 (GND), U1.40 (GND), U1.41 (GND), U2.1 (GND)
IO0: R7.1, SW4.1, U1.27 (IO0)
LCD_BL: J2.8, U1.11 (IO18)
LCD_CS: J2.7, U1.10 (IO17)
LCD_DC: J2.6, U1.8 (IO15)
LCD_RST: J2.5, U1.9 (IO16)
LED_DIN: J7.2, LED1.4 (DIN), U1.25 (IO48)
LED_VDD: C4.1, D2.1 (K), LED1.1 (VDD)
OW: J5.2, JP1.1 (A), R4.1, U1.7 (IO7)
OW2: JP1.3 (B), R5.1, U1.38 (IO2)
PS_ON: J1.16 (PS_ON), Q1.3 (D)
PWR_OK: J1.8 (PWR_OK), R2.1
PWR_OK_SENSE: R2.2, R3.1, U1.5 (IO5)
RELAY_CTRL: Q1.1 (G), R1.1, U1.4 (IO4)
RXD0: J9.2, U1.36 (RXD0)
SCL_SCK: J2.3, U1.17 (IO9)
SDA_MOSI: J2.4, U1.12 (IO8)
T2_SIG: J6.2, JP1.2 (C)
TXD0: J9.1, U1.37 (TXD0)
USB_DN: J3.A7 (D-), J3.B7 (D-), U1.13 (USB_D-)
USB_DP: J3.A6 (D+), J3.B6 (D+), U1.14 (USB_D+)
VBUS: D1.2 (A), J3.A4 (VBUS), J3.A9 (VBUS), J3.B4 (VBUS), J3.B9 (VBUS)

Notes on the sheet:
BC250 Front Controller - ESP32-S3 PCBA (fully assembled at JLCPCB)
PSU ATX 24-pin plug -> J1. 5VSB feeds the 5V rail and U2 (3V3) at all times; VBUS only through D1.
Q1 pulls PS_ON low (PSU ON) while GPIO4 is HIGH or floating (R1 pull-up) -> PSU stays on when the ESP32 is dead.
GPIO4 LOW -> PSU off. Same polarity as the relay-module wiring: keep relay_inverted: "true" in the yaml.
PWR_OK 5V -> R2/R3 -> GPIO5. T1 on GPIO7 (R4 pull-up); T2 on GPIO7 via JP1 1-2 (default) or GPIO2 via JP1 2-3 (R5).
Both temp inputs work as DS18B20 (1-wire) or as 10k NTC (ADC, 4.7k reference) - see README.
J2: ST7789 module on pins 1-8, or SSD1306 OLED on pins 1-4 (GND VCC SCL SDA). J7 = external WS2812 in parallel with LED1.
Hand-soldered by the user (not in the JLCPCB BOM): U1 module, J2 socket, LED1. Everything else is Economic-assembly eligible.

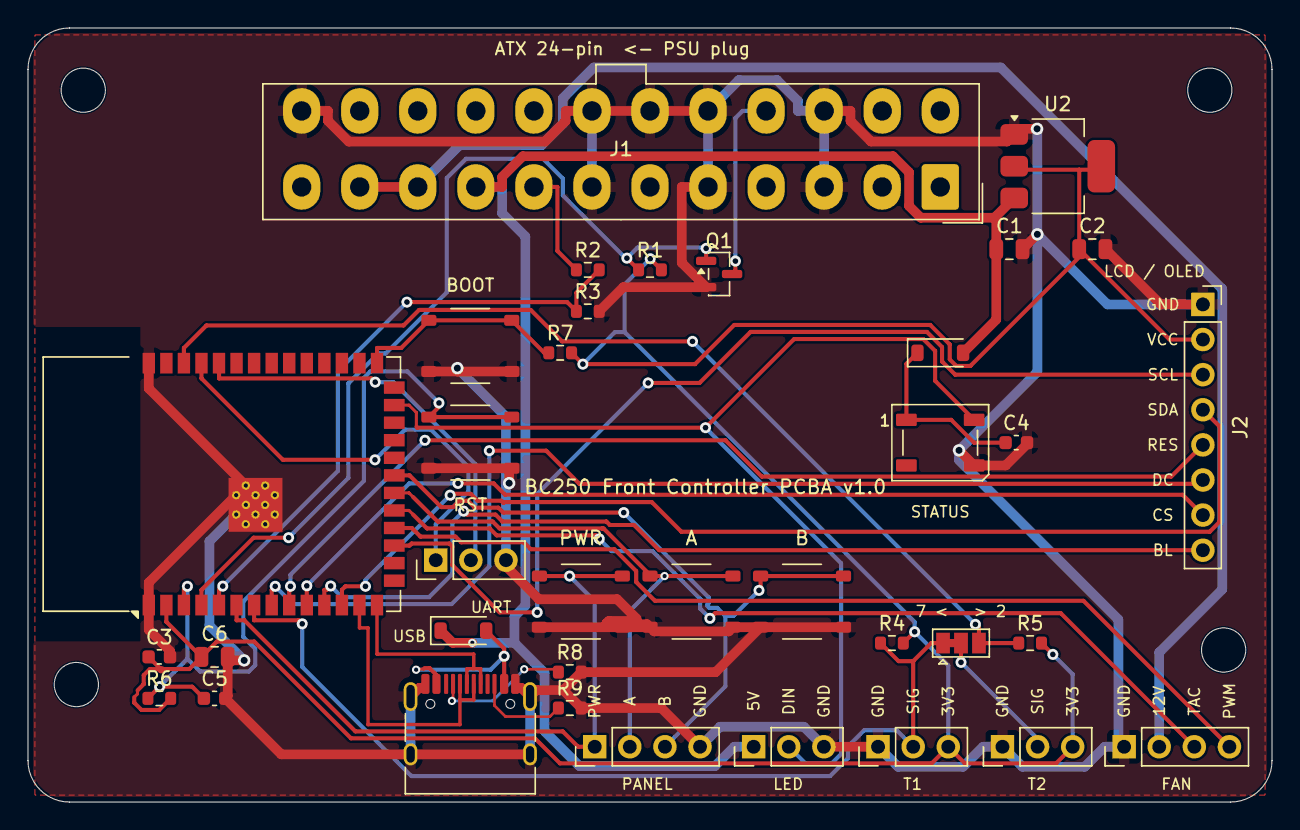
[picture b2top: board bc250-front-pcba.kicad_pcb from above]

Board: 2 copper layers, 90.0 x 56.0 mm, 40 parts (0 on the bottom side), 33 nets.

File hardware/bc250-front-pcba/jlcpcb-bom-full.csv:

Comment,Designator,Footprint,LCSC Part #
10uF,"C1,C2,C6",C_0805_2012Metric,C15850
100nF,"C3,C4",C_0603_1608Metric,C14663
1uF,C5,C_0603_1608Metric,C15849
B5819W,D1,D_SOD-123,C8598
1N4148W,D2,D_SOD-123,C81598
ATX 24-pin,J1,Molex_Mini-Fit_Jr_5566-24A_2x12_P4.20mm_Vertical,C114088
LCD / OLED,J2,PinSocket_1x08_P2.54mm_Vertical,C27438
USB-C,J3,USB_C_Receptacle_HRO_TYPE-C-31-M-12,C165948
FAN,J4,PinHeader_1x04_P2.54mm_Vertical,C124378
T1,J5,PinHeader_1x03_P2.54mm_Vertical,C49257
T2,J6,PinHeader_1x03_P2.54mm_Vertical,C49257
LED,J7,PinHeader_1x03_P2.54mm_Vertical,C49257
PANEL,J8,PinHeader_1x04_P2.54mm_Vertical,C124378
WS2812B,LED1,LED_WS2812B_PLCC4_5.0x5.0mm_P3.2mm,C2761795
AO3400A,Q1,SOT-23,C20917
10k,"R1,R2,R3,R6,R7",R_0603_1608Metric,C25804
4.7k,"R4,R5",R_0603_1608Metric,C23162
5.1k,"R8,R9",R_0603_1608Metric,C23186
PWR,SW1,SW_TS-1187A,C318884
MENU A,SW2,SW_TS-1187A,C318884
MENU B,SW3,SW_TS-1187A,C318884
BOOT,SW4,SW_TS-1187A,C318884
RESET,SW5,SW_TS-1187A,C318884
ESP32-S3-WROOM-1-N16R8,U1,ESP32-S3-WROOM-1_edge,C2913202
AMS1117-3.3,U2,SOT-223-3_TabPin2,C6186

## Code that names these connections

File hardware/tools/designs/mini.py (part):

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     "N-MOSFET pulls PS_ON low (PSU on); gate pulled up -> fail-safe on"),
    ("R1", R0603, "10k", 53.0, 30.5, 0, {1: "RELAY_CTRL", 2: "+3V3"}, "gate pull-up (PSU on while ESP32 is dead)"),
    # --- top edge ---
    ("J4", "PinHeader_1x04_P2.54mm_Vertical", "FAN", 3.0, TOP_Y, 90, {1: "GND", 2: "+12V", 3: "FAN_TACH", 4: "FAN_PWM"},
     "4-pin PWM fan: GND 12V TACH PWM"),
    # --- bottom edge ---
    ("J8", "PinHeader_1x04_P2.54mm_Vertical", "PANEL", 4.0, BOT_Y, 90, {1: "BTN_PWR", 2: "BTN_A", 3: "BTN_B", 4: "GND"},
     "front-panel buttons: PWR A B GND"),
    ("J7", "PinHeader_1x03_P2.54mm_Vertical", "LED", 15.5, BOT_Y, 90, {1: "LED_VDD", 2: "LED_DIN", 3: "GND"},
     "external WS2812 status LED: 5V(4.3V) DIN GND"),
    ("J5", "PinHeader_1x03_P2.54mm_Vertical", "T1", 24.5, BOT_Y, 90, {1: "GND", 2: "OW", 3: "+3V3"},
     "DS18B20 #1 (GPU): GND DQ VDD"),
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SCH_NOTES = [
    "BC250 Front Controller - ESP32-S3 DevKitC-1 mini (66 x 50 mm)",
    "PSU ATX 24-pin plug -> J1.  5VSB -> DevKit 5V pin (its own LDO makes 3V3).  12V only feeds the fan header.",
    "Q1 pulls PS_ON low (PSU ON) while GPIO4 is HIGH or floating (R1 pull-up) -> PSU stays on when the ESP32 is dead.",
    "GPIO4 LOW -> PSU off.  Same polarity as the relay-module wiring: keep  relay_inverted: \"true\"  in the yaml.",
    "PWR_OK 5V -> R2 10k / R3 20k -> 3.3 V -> GPIO5.   DS18B20 x2 on GPIO7 (R4).   FAN TACH -> R6 10k -> GPIO11.",
    "J7 5V pin is fed through D2 (~4.3 V) so a 3.3 V data line is a valid HIGH for a WS2812B.  J2 = ST7789 via wires.",
]

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
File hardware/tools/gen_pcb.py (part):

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     {1: "PS_ON", 4: "GND", 2: "+5V", 5: "RELAY_COIL"},
     "5V SPDT relay; COM=PS_ON, NC=GND (fail-safe: PSU stays on when ESP32 is dead)"),
    ("Q1", "TO-92_Inline", "S8050", 69.0, 20.4, 0,
     {1: "GND", 2: "Q1_B", 3: "RELAY_COIL"}, "NPN relay driver, pins E-B-C"),
    ("D1", "D_DO-35_SOD27_P7.62mm_Horizontal", "1N4148", 76.5, 21.0, 0,
     {1: "+5V", 2: "RELAY_COIL"}, "relay flyback diode (cathode band = pin 1 = +5V)"),
    ("R1", "R_Axial_DIN0207_L6.3mm_D2.5mm_P7.62mm_Horizontal", "1k", RES_X, RES_Y0 + 0 * RES_PITCH, 0,
     {1: "RELAY_CTRL", 2: "Q1_B"}, "base resistor"),
    ("R2", "R_Axial_DIN0207_L6.3mm_D2.5mm_P7.62mm_Horizontal", "10k", RES_X, RES_Y0 + 1 * RES_PITCH, 0,
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     {1: "GND", 2: "+3V3", 3: "SCL_SCK", 4: "SDA_MOSI"},
     "0.96in I2C OLED: GND VCC SCL SDA"),
    ("J4", "PinHeader_1x04_P2.54mm_Vertical", "FAN", 82.0, BOT_Y, 90,
     {1: "GND", 2: "+12V", 3: "FAN_TACH", 4: "FAN_PWM"}, "PC 4-pin PWM fan: GND 12V TACH PWM"),
    ("J5", "PinHeader_1x03_P2.54mm_Vertical", "T1 GPU", 64.0, BOT_Y, 90,
     {1: "GND", 2: "OW", 3: "+3V3"}, "DS18B20 #1 (GPU heatsink): GND DQ VDD"),
    ("J6", "PinHeader_1x03_P2.54mm_Vertical", "T2 CASE", 73.0, BOT_Y, 90,
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
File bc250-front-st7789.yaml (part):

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#
# ── 핀맵 (기존 그대로) ─────────────────────────────────────────────────────────────
#  GPIO4  릴레이 IN            GPIO10 팬 PWM 출력 (25kHz)
#  GPIO5  PWR_OK 감지(분압)     GPIO11 팬 타코 입력
#  GPIO6  전원 버튼(GND로)      GPIO12 메뉴 버튼A (다음 화면 / 다음 항목 / 값 올리기 +)
#  GPIO7  DS18B20 원와이어      GPIO13 메뉴 버튼B (선택·확정)
#  GPIO48 WS2812 상태 LED       GPIO14 메뉴 버튼C (이전 화면 / 이전 항목 / 값 내리기 −)  ← 2026-08-31 추가
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#     바뀌면 영구히 깨진 채 남았음 → 이 복구가 그걸 메꾼다)
#  · 화면 하드 복구(script lcd_reset): RST 핀으로 LCD를 완전히 리셋하고 초기화 시퀀스 전체를 다시 보냄 —
#    메뉴 "화면 복구" / 웹·HA "화면 복구" 버튼. 약 0.4초 화면이 꺼졌다 켜진다.
#    → 이를 위해 GPIO15(DC)도 output.lcd_dc 로 공유(allow_other_uses), GPIO16(RST)은 이미 공유 중.
#  · 화면 갱신 1초 → 2초: 한 프레임(240×320×16bit=153KB) 쓰는 데 약 140ms 동안 메인 루프가 멈춰(버튼 반응
#    지연·짧은 누름이 길게 잡히는 원인) 절반으로 줄임. 값들은 어차피 5초마다 갱신. 버튼 조작은 즉시 갱신.
#  · SPI 클럭 substitutions lcd_data_rate 로 노출(기본 20MHz). 점퍼선이 길어 계속 깨지면 10MHz 로 낮춰 볼 것.
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  # (RST로 재부팅하면 LCD가 이미 안정된 상태라 정상). 그래서 드라이버 초기화(priority 400) 전에
  # LCD RST(GPIO16)를 1초간 LOW로 잡아 두고(그 사이 LCD·릴레이로 켜진 PSU 전원도 안정) → HIGH →
  # 200ms 뒤에 드라이버가 초기화하도록 한다. 기다리는 동안은 백라이트를 꺼서 백지 화면이 안 보이게 한다.
  # GPIO16은 output.lcd_rst 와 display.reset_pin 이 공유 (둘 다 allow_other_uses: true).
  on_boot:
    # ── 전원 정책 (2026-09-01) ── 릴레이는 ALWAYS_OFF(=서버 ON)로 셋업(800)됨. 소프트 재부팅(OTA·재시작 버튼·
    # 안전 모드·워치독)이고 마지막 상태가 "서버 꺼짐"이면 여기서 다시 끈다. 콜드 부팅(5VSB/AC 투입, RST 버튼도
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      - timing: [ON for at least 1.2s]
        then: [display_menu.hide: settings_menu]

  - platform: template      # PWR_OK(회색) 10k+10k 분압 → GPIO5 를 ADC 로 읽어 판정 (2026-09-01, 예전엔 디지털 입력)
    id: psu_ok
    name: "PSU 실제 켜짐"
    device_class: power
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    offset_height: 0
    offset_width: 0
    cs_pin: GPIO17
    dc_pin: {number: GPIO15, allow_other_uses: true}      # output.lcd_dc 와 공유 (복구 스크립트용)
    reset_pin: {number: GPIO16, allow_other_uses: true}   # output.lcd_rst 와 공유 (부팅 때 긴 리셋·하드 복구)
    data_rate: ${lcd_data_rate}   # 기본 20MHz. 화면이 계속 깨지면 substitutions 에서 10MHz 로
    rotation: 0
    # 2026-09-01 1s → 2s: 한 프레임 쓰는 ~140ms 동안 루프가 멈추는 횟수를 절반으로. 버튼·전원 조작은 즉시 갱신됨
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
